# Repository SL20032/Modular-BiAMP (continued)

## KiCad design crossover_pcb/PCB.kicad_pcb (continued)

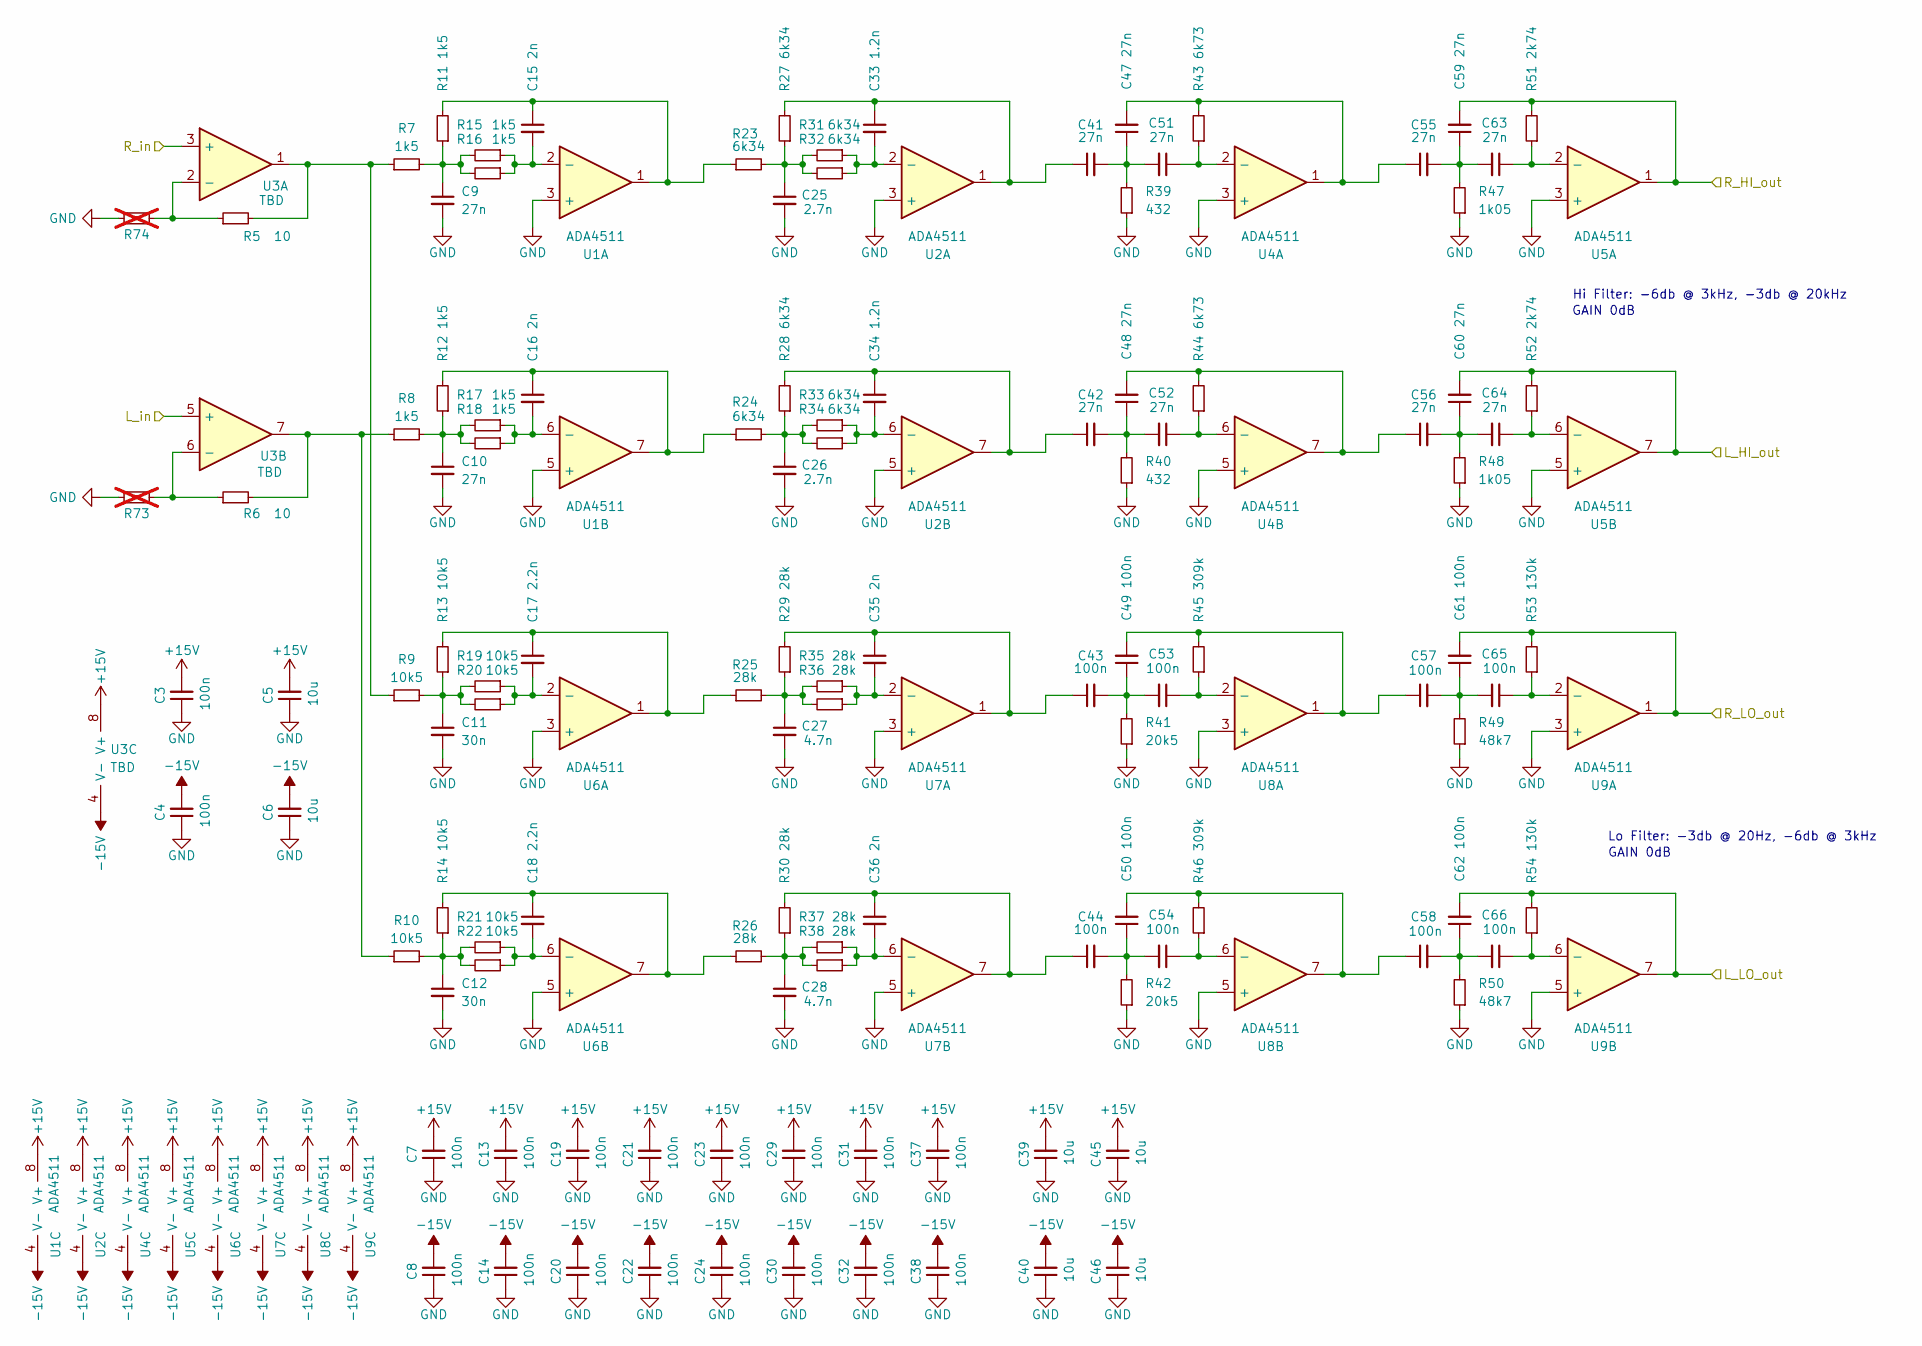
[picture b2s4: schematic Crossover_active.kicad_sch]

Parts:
C3, C4, C7, C8, C13, C14, C19, C20, C21, C22, C23, C24, C29, C30, C31, C32, C37, C38: 100n; C_0805_2012Metric_Pad1.18x1.45mm_HandSolder
C5, C6, C39, C40, C45, C46: 10u; C_0805_2012Metric_Pad1.18x1.45mm_HandSolder
C9, C10, C41, C42, C47, C48, C51, C52, C55, C56, C59, C60, C63, C64: 27n; C_Rect_L7.2mm_W2.5mm_P5.00mm_FKS2_FKP2_MKS2_MKP2
C11, C12: 30n; C_Rect_L7.2mm_W2.5mm_P5.00mm_FKS2_FKP2_MKS2_MKP2
C15, C16, C35, C36: 2n; C_Rect_L7.2mm_W2.5mm_P5.00mm_FKS2_FKP2_MKS2_MKP2
C17, C18: 2.2n; C_Rect_L7.2mm_W2.5mm_P5.00mm_FKS2_FKP2_MKS2_MKP2
C25, C26: 2.7n; C_Rect_L7.2mm_W2.5mm_P5.00mm_FKS2_FKP2_MKS2_MKP2
C27, C28: 4.7n; C_Rect_L7.2mm_W2.5mm_P5.00mm_FKS2_FKP2_MKS2_MKP2
C33, C34: 1.2n; C_Rect_L7.2mm_W2.5mm_P5.00mm_FKS2_FKP2_MKS2_MKP2
C43, C44, C49, C50, C53, C54, C57, C58, C61, C62, C65, C66: 100n; C_Rect_L7.2mm_W2.5mm_P5.00mm_FKS2_FKP2_MKS2_MKP2
R5, R6: 10; R_0805_2012Metric_Pad1.20x1.40mm_HandSolder
R7, R8, R11, R12, R15, R16, R17, R18: 1k5; R_0805_2012Metric_Pad1.20x1.40mm_HandSolder
R9, R10, R13, R14, R19, R20, R21, R22: 10k5; R_0805_2012Metric_Pad1.20x1.40mm_HandSolder
R23, R24, R27, R28, R31, R32, R33, R34: 6k34; R_0805_2012Metric_Pad1.20x1.40mm_HandSolder
R25, R26, R29, R30, R35, R36, R37, R38: 28k; R_0805_2012Metric_Pad1.20x1.40mm_HandSolder
R39, R40: 432; R_0805_2012Metric_Pad1.20x1.40mm_HandSolder
R41, R42: 20k5; R_0805_2012Metric_Pad1.20x1.40mm_HandSolder
R43, R44: 6k73; R_0805_2012Metric_Pad1.20x1.40mm_HandSolder
R45, R46: 309k; R_0805_2012Metric_Pad1.20x1.40mm_HandSolder
R47, R48: 1k05; R_0805_2012Metric_Pad1.20x1.40mm_HandSolder
R49, R50: 48k7; R_0805_2012Metric_Pad1.20x1.40mm_HandSolder
R51, R52: 2k74; R_0805_2012Metric_Pad1.20x1.40mm_HandSolder
R53, R54: 130k; R_0805_2012Metric_Pad1.20x1.40mm_HandSolder
R73, R74: R_0805_2012Metric_Pad1.20x1.40mm_HandSolder; not fitted
U1, U2, U4, U5, U6, U7, U8, U9: ADA4511; SO-8_3.9x4.9mm_P1.27mm
U3: TBD; SO-8_3.9x4.9mm_P1.27mm

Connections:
+15V: C3.2, C5.2, C7.2, C13.2, C19.2, C21.2, C23.2, C29.2, C31.2, C37.2, C39.2, C45.2, U1.8 (V+), U2.8 (V+), U3.8 (V+), U4.8 (V+), U5.8 (V+), U6.8 (V+), U7.8 (V+), U8.8 (V+), U9.8 (V+); also elsewhere on the board
-15V: C4.2, C6.2, C8.2, C14.2, C20.2, C22.2, C24.2, C30.2, C32.2, C38.2, C40.2, C46.2, U1.4 (V-), U2.4 (V-), U3.4 (V-), U4.4 (V-), U5.4 (V-), U6.4 (V-), U7.4 (V-), U8.4 (V-), U9.4 (V-); also elsewhere on the board
/Crossover/L_HI_out: C60.2, R52.2, U5.7; also elsewhere on the board
/Crossover/L_LO_out: C62.2, R54.2, U9.7; also elsewhere on the board
/Crossover/R_HI_out: C59.2, R51.2, U5.1; also elsewhere on the board
/Crossover/R_LO_out: C61.2, R53.2, U9.1; also elsewhere on the board
/Volume Control/L_VCtrl: U3.5 (+); also elsewhere on the board
/Volume Control/R_VCtrl: U3.3 (+); also elsewhere on the board
GND: C3.1, C4.1, C5.1, C6.1, C7.1, C8.1, C9.2, C10.2, C11.2, C12.2, C13.1, C14.1, C19.1, C20.1, C21.1, C22.1, C23.1, C24.1, C25.2, C26.2, C27.2, C28.2, C29.1, C30.1, C31.1, C32.1, C37.1, C38.1, C39.1, C40.1, C45.1, C46.1, R39.1, R40.1, R41.1, R42.1, R47.1, R48.1, R49.1, R50.1, R73.1, R74.1, U1.3 (+), U1.5 (+), U2.3 (+), U2.5 (+), U4.3 (+), U4.5 (+), U5.3 (+), U5.5 (+), U6.3 (+), U6.5 (+), U7.3 (+), U7.5 (+), U8.3 (+), U8.5 (+), U9.3 (+), U9.5 (+); also elsewhere on the board
unnamed: C9.1, R7.2, R11.1, R15.2, R16.2
unnamed: C10.1, R8.2, R12.1, R17.2, R18.2
unnamed: C11.1, R9.2, R13.1, R19.2, R20.2
unnamed: C12.1, R10.2, R14.1, R21.2, R22.2
unnamed: C15.1, R11.2, R23.1, U1.1
unnamed: C16.1, R12.2, R24.1, U1.7
unnamed: C17.1, R13.2, R25.1, U6.1
unnamed: C18.1, R14.2, R26.1, U6.7
unnamed: C25.1, R23.2, R27.1, R31.2, R32.2
unnamed: C26.1, R24.2, R28.1, R33.2, R34.2
unnamed: C27.1, R25.2, R29.1, R35.2, R36.2
unnamed: C28.1, R26.2, R30.1, R37.2, R38.2
unnamed: C33.1, C41.1, R27.2, U2.1
unnamed: C34.1, C42.1, R28.2, U2.7
unnamed: C35.1, C43.1, R29.2, U7.1
unnamed: C36.1, C44.1, R30.2, U7.7
unnamed: C41.2, C47.1, C51.2, R39.2
unnamed: C42.2, C48.1, C52.2, R40.2
unnamed: C43.2, C49.1, C53.2, R41.2
unnamed: C44.2, C50.1, C54.2, R42.2
unnamed: C47.2, C55.1, R43.2, U4.1
unnamed: C48.2, C56.1, R44.2, U4.7
unnamed: C49.2, C57.1, R45.2, U8.1
unnamed: C50.2, C58.1, R46.2, U8.7
unnamed: C55.2, C59.1, C63.2, R47.2
unnamed: C56.2, C60.1, C64.2, R48.2
unnamed: C57.2, C61.1, C65.2, R49.2
unnamed: C58.2, C62.1, C66.2, R50.2
unnamed: R5.2, R7.1, R9.1, U3.1
unnamed: R6.2, R8.1, R10.1, U3.7
unnamed: C15.2, R15.1, R16.1, U1.2 (-)
unnamed: C16.2, R17.1, R18.1, U1.6 (-)
unnamed: C33.2, R31.1, R32.1, U2.2 (-)
unnamed: C34.2, R33.1, R34.1, U2.6 (-)
unnamed: R5.1, R74.2, U3.2 (-)
unnamed: R6.1, R73.2, U3.6 (-)
unnamed: C51.1, R43.1, U4.2 (-)
unnamed: C52.1, R44.1, U4.6 (-)
unnamed: C63.1, R51.1, U5.2 (-)
unnamed: C64.1, R52.1, U5.6 (-)
unnamed: C17.2, R19.1, R20.1, U6.2 (-)
unnamed: C18.2, R21.1, R22.1, U6.6 (-)
unnamed: C35.2, R35.1, R36.1, U7.2 (-)
unnamed: C36.2, R37.1, R38.1, U7.6 (-)
unnamed: C53.1, R45.1, U8.2 (-)
unnamed: C54.1, R46.1, U8.6 (-)
unnamed: C65.1, R53.1, U9.2 (-)
unnamed: C66.1, R54.1, U9.6 (-)

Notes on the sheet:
GAIN 0dB
Hi Filter: -6db @ 3kHz, -3db @ 20kHz
Lo Filter: -3db @ 20Hz, -6db @ 3kHz

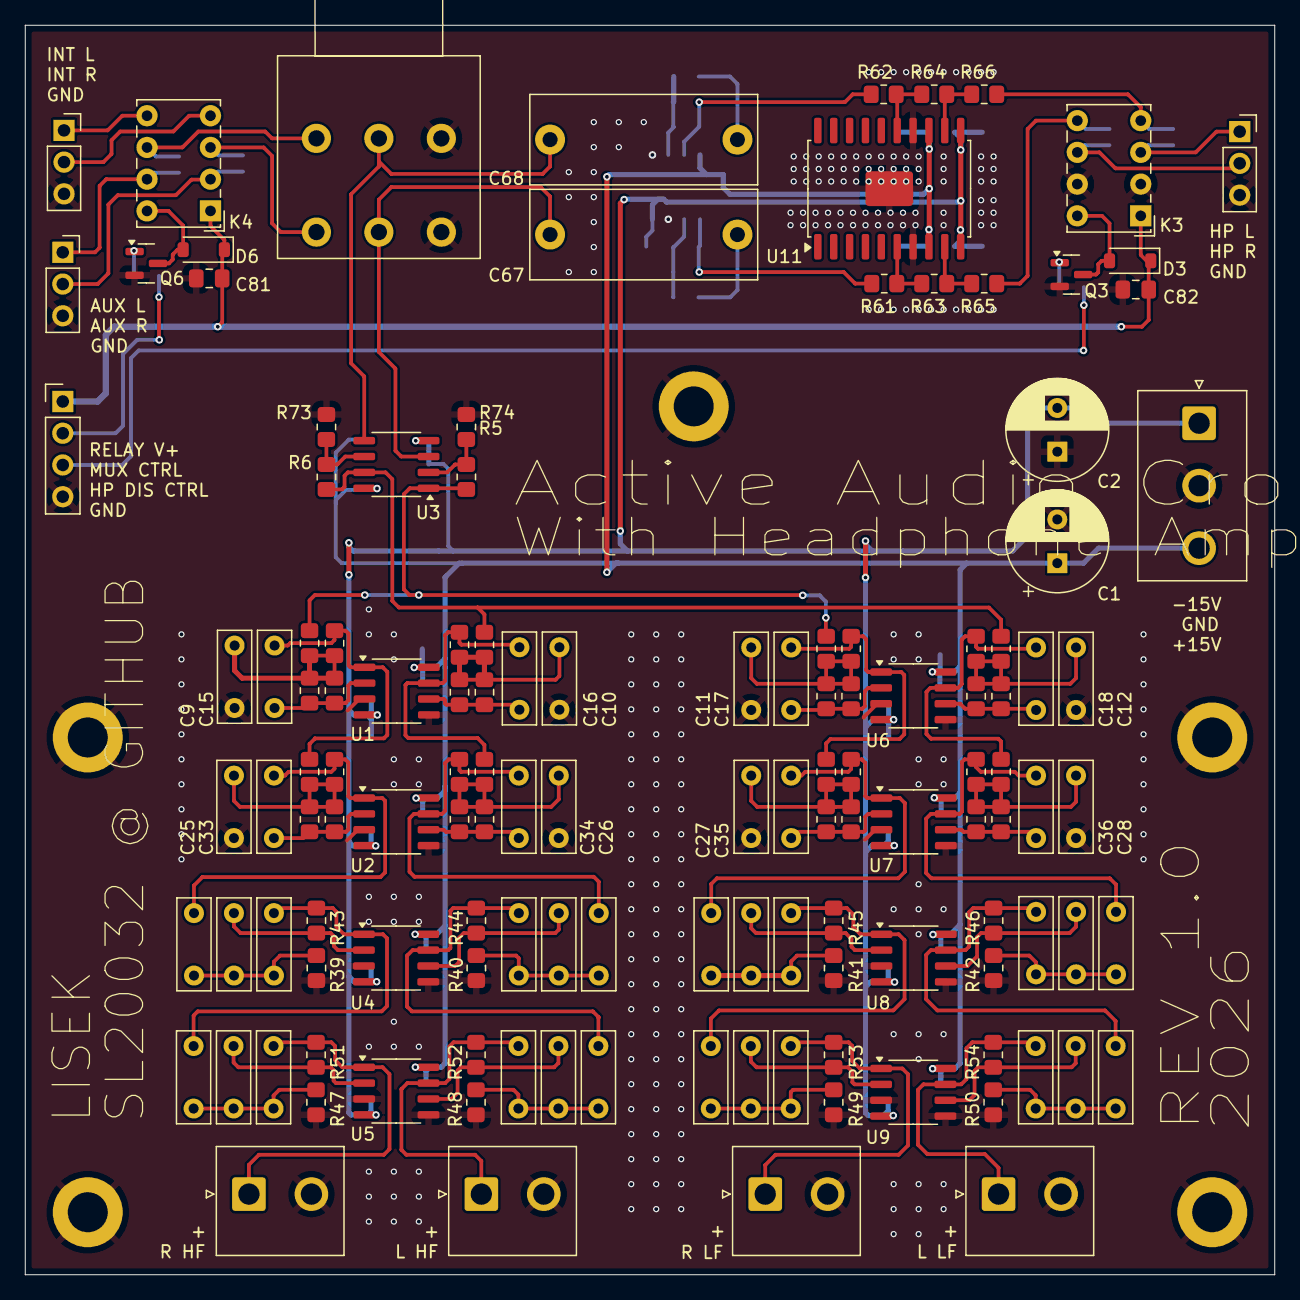
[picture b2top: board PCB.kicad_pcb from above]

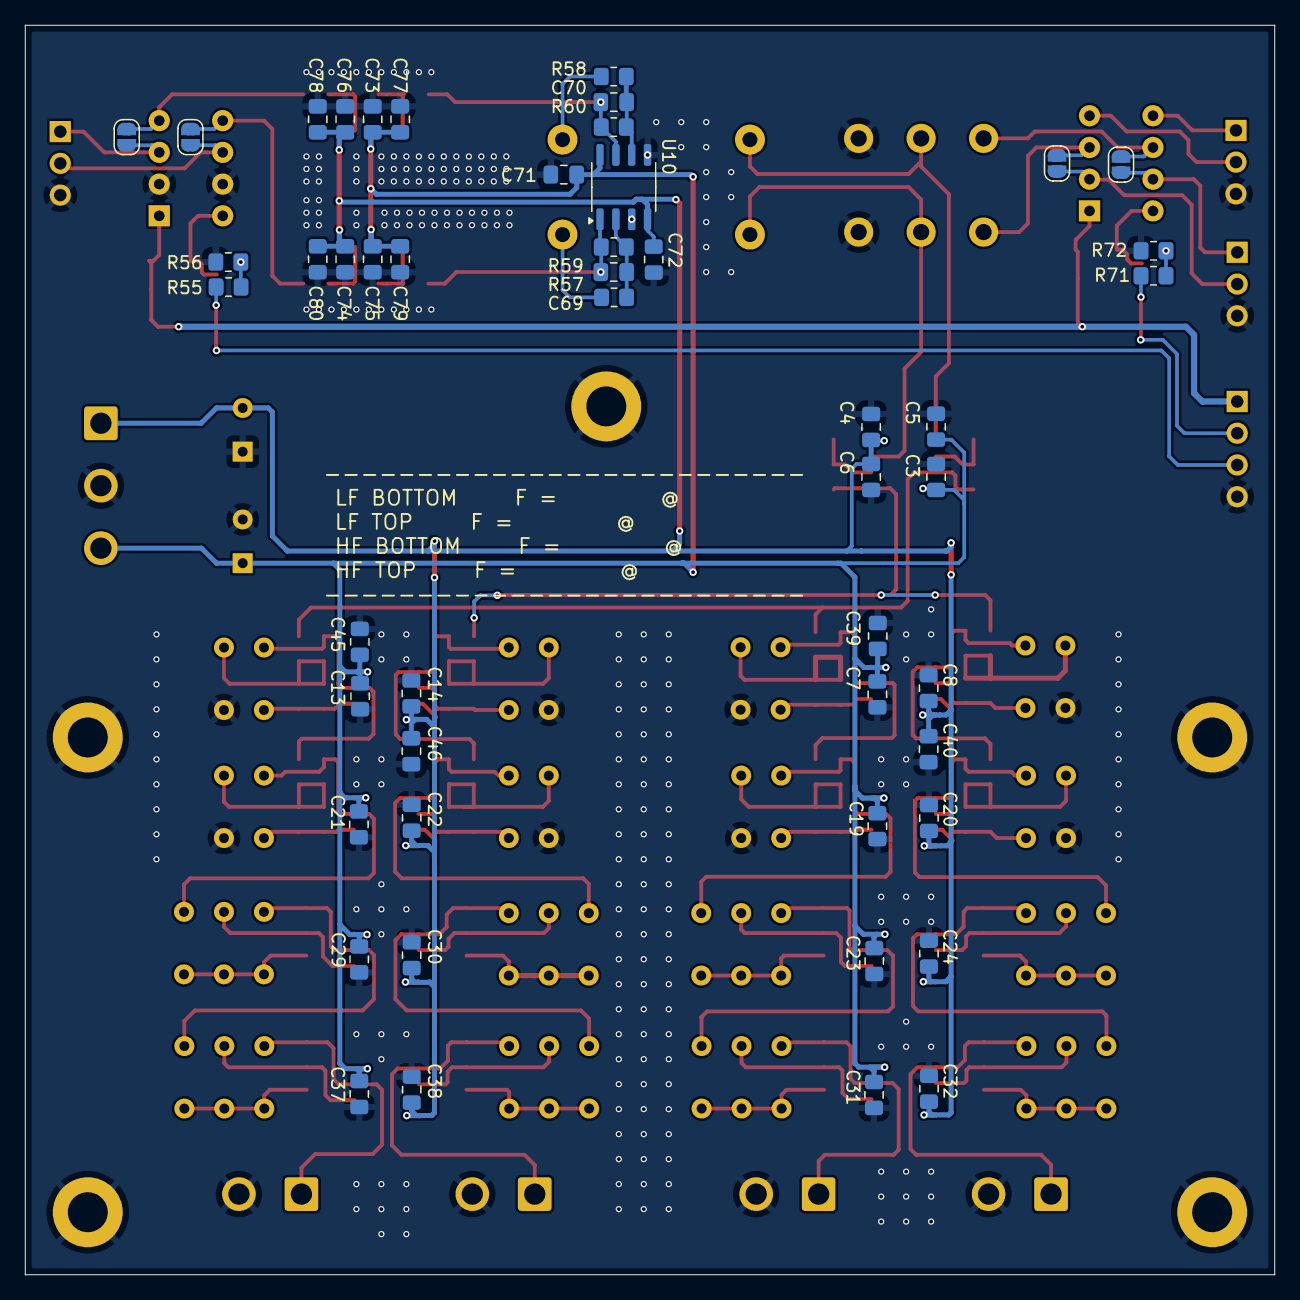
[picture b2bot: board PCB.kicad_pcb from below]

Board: 2 copper layers, 100.0 x 100.0 mm, 184 parts (49 on the bottom side), 84 nets.

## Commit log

2026-04-20 changed README.md
